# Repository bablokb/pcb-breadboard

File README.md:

Project pcb-breadboard
======================

Overview
--------

This project contains the KiCAD files for a breadboard with

  - two (connected) power rails
  - power connectors (JST and barrel-jack)
  - on/off slider
  - two Grove connectors

In contrast to normal breadboards, the individual rails are not
paired, but the design allows to easily cut the rails on the back.

The schematic:

The layout:

Production Files
----------------

The production files are in `gerber.zip`.

License
-------

Shield: [![CC BY-SA 4.0][cc-by-sa-shield]][cc-by-sa]

This work is licensed under a
[Creative Commons Attribution-ShareAlike 4.0 International
License][cc-by-sa].

[![CC BY-SA 4.0][cc-by-sa-image]][cc-by-sa]

[cc-by-sa]: http://creativecommons.org/licenses/by-sa/4.0/
[cc-by-sa-image]: https://licensebuttons.net/l/by-sa/4.0/88x31.png
[cc-by-sa-shield]:
https://img.shields.io/badge/License-CC%20BY--SA%204.0-lightgrey.svg

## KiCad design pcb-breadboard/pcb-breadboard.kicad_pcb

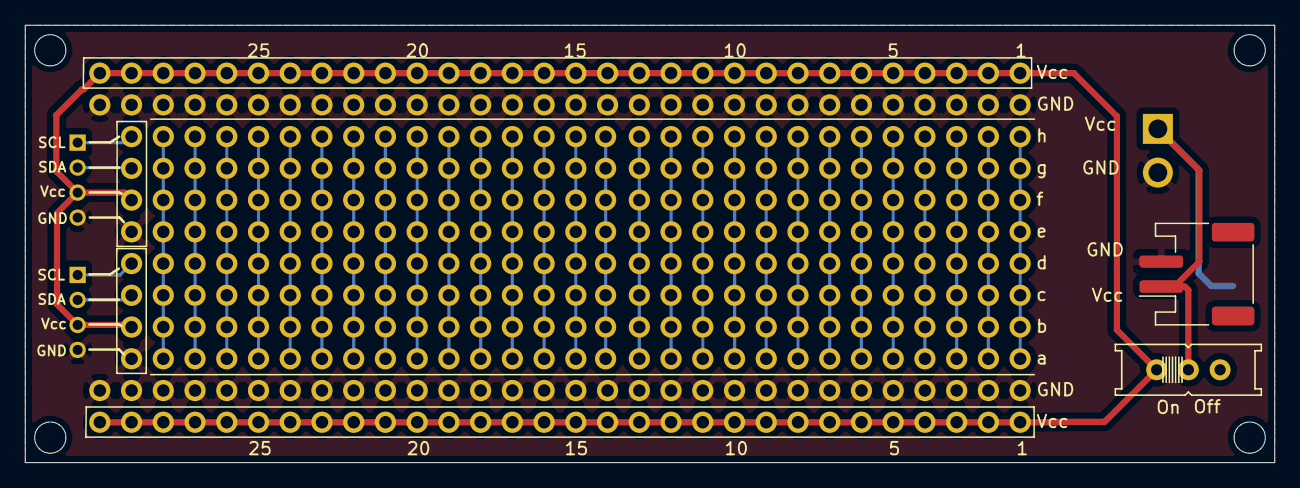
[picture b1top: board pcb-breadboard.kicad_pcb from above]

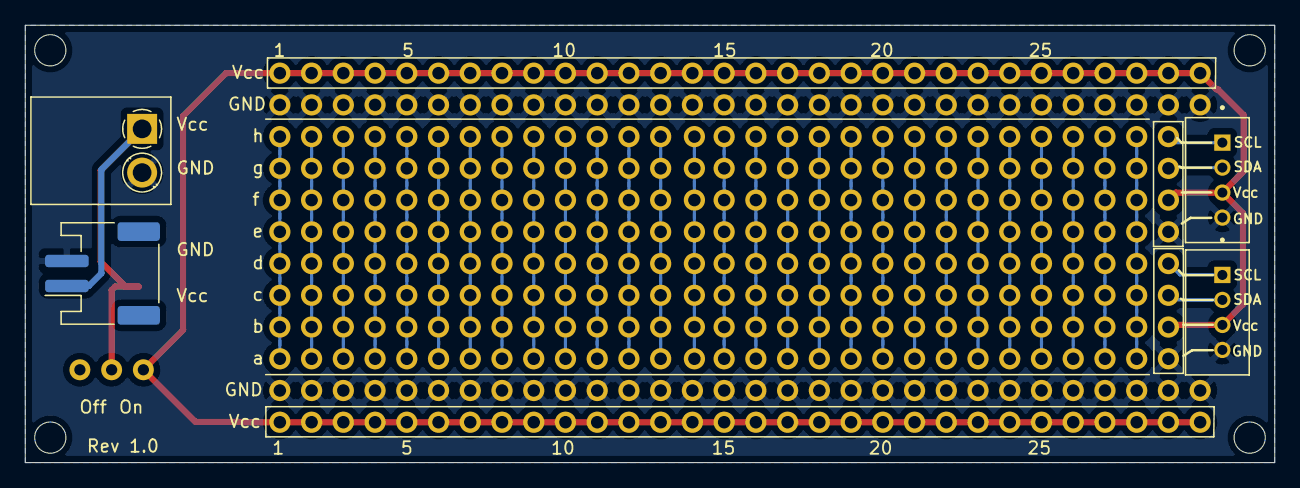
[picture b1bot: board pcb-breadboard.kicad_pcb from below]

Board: 2 copper layers, 100.0 x 35.0 mm, 42 parts (4 on the bottom side), 7 nets.

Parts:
B1, B2, B3, B4, B5, B6, B7, B8, B9, B10, B11, B12, B13, B14, B15, B16, B17, B18, B19, B20, B21, B22, B23, B24, B25, B26, B27, B28: BB_Strip; bb_strip
B31, B32: BB_Strip_PWR_GND; bb_strip_pwr_gnd
H1, H2, H3, H4: MountingHole; MountingHole_2.5mm
J1, J3: Conn_01x04_Male; Proto_Area_04x01
J2, J4: Grove; grove_vertical
J5: AKL_PWR; TerminalBlock_MetzConnect_Type182_PT11302HBBN_1x02_P3.50mm_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
J6, J7: JST_PWR; JST_PH_S2B-PH-SM4-TB_1x02-1MP_P2.00mm_Horizontal
S1: EG1218

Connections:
GND: B31.2, B32.2, J1.4, J2.4, J3.4, J4.4, J5.2, J6.2, J7.2
unnamed: J1.1, J2.1
unnamed: J1.2, J2.2
unnamed: J3.1, J4.1
unnamed: J3.2, J4.2
unnamed: J5.1, J6.1, J7.1, S1.P
VCC: B31.1, B32.1, J1.3, J2.3, J3.3, J4.3, S1.O

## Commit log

2021-12-11 added content
2022-02-02 minor markup change
